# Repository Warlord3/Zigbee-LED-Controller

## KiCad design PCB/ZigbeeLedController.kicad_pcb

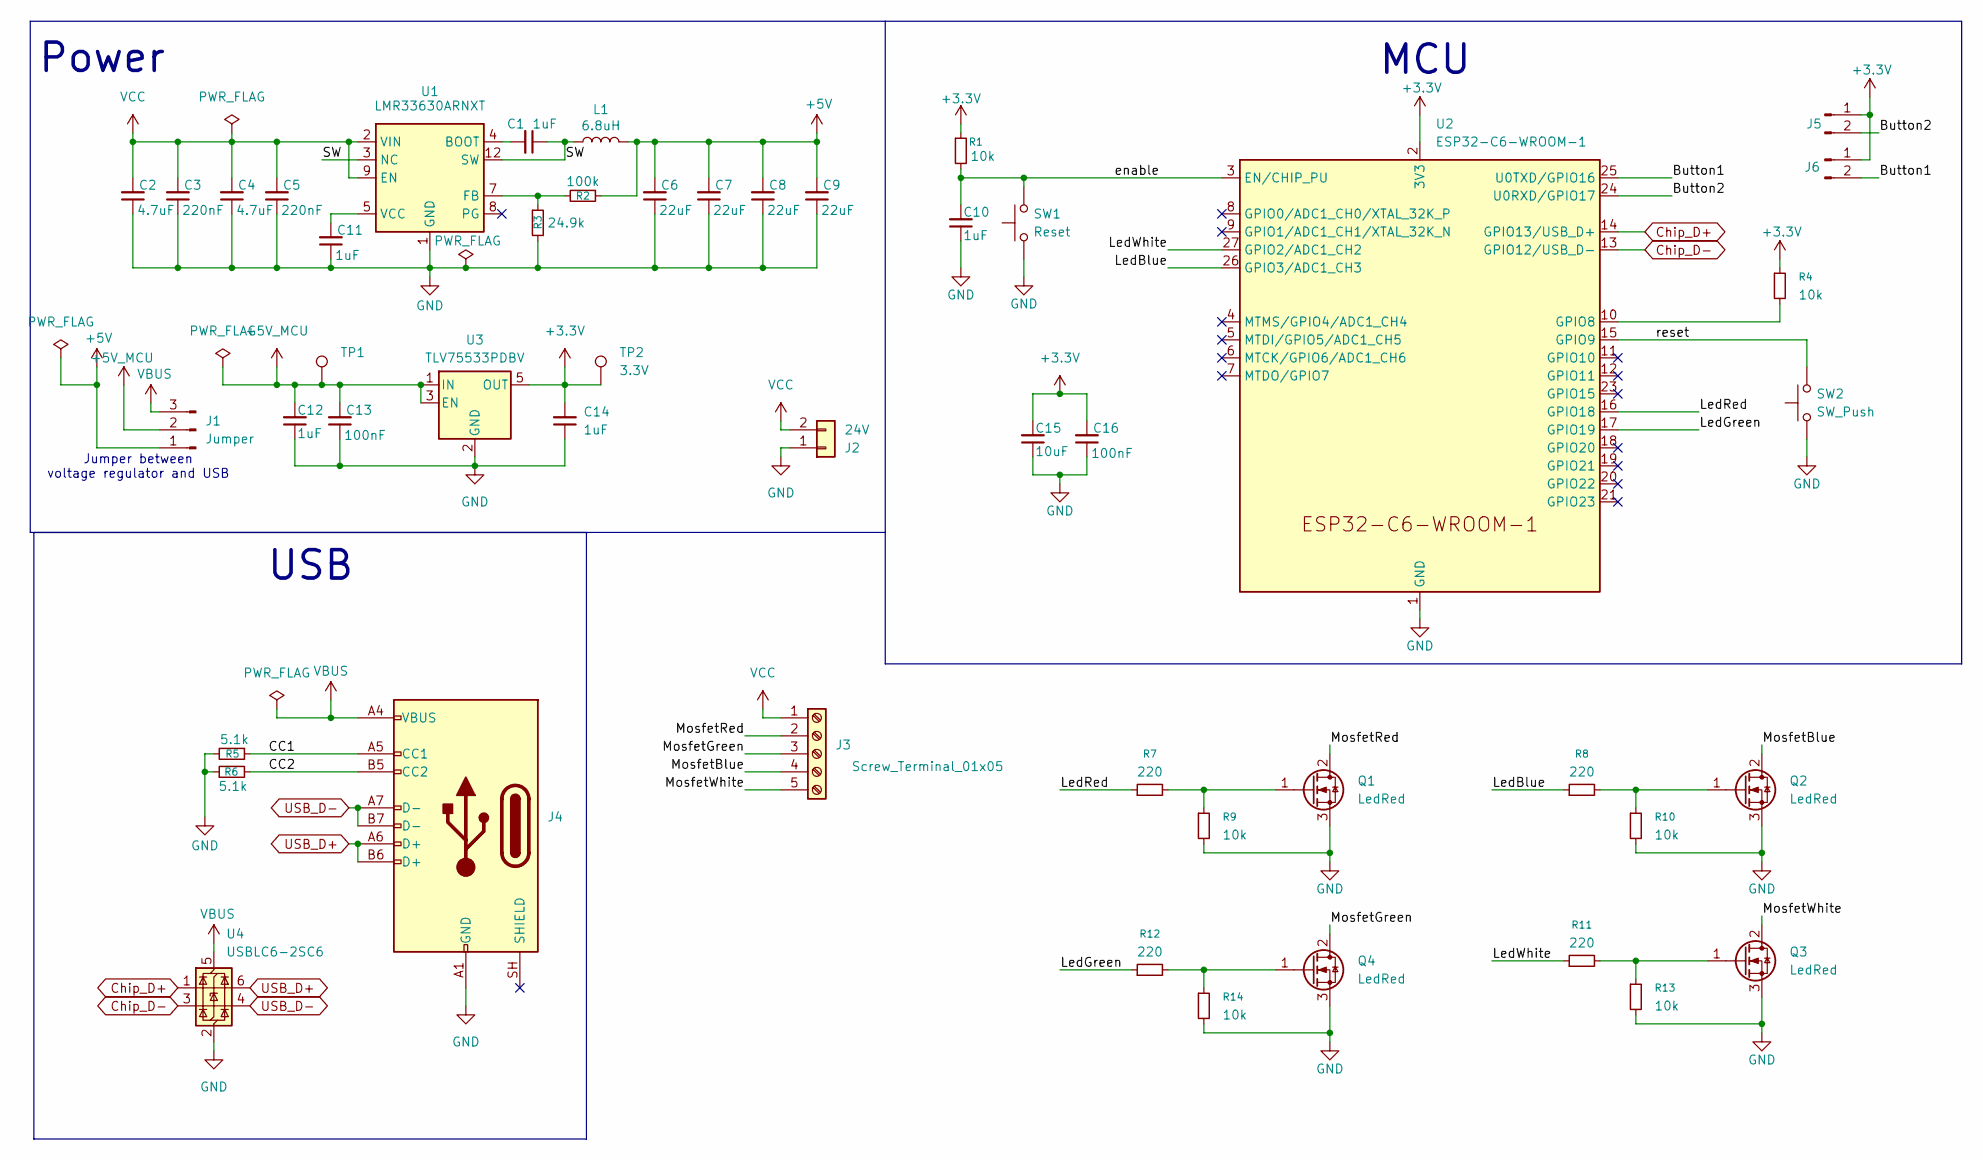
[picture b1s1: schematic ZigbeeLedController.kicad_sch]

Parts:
C1: 1uF; C_0603_1608Metric; MPN C29936
C2, C4: 4.7uF; C_0805_2012Metric; MPN C98192
C3, C5: 220nF; C_0603_1608Metric; MPN C307462
C6, C7, C8, C9: 22uF; C_1210_3225Metric; MPN C380537
C10, C12, C14: 1uF; C_0603_1608Metric; MPN C95843
C11: 1uF; C_0603_1608Metric; MPN C5199872
C13, C16: 100nF; C_0402_1005Metric; MPN C541406
C15: 10uF; C_0603_1608Metric; MPN C19702
J1: Jumper; PinHeader_1x03_P2.54mm_Vertical
J2: 24V; TerminalBlock_MaiXu_MX126-5.0-02P_1x02_P5.00mm; MPN C55469890
J3: Screw_Terminal_01x05; TerminalBlock_CUI_TB007-508-05_1x05_P5.08mm_Horizontal; MPN C2927513
J4: USB_C_Receptacle_USB2.0_14P; USB_C_Receptacle_G-Switch_GT-USB-7010ASV; MPN C2988369
J5, J6: Conn_01x02_Pin; PinHeader_1x02_P2.54mm_Vertical
L1: 6.8uH; L_TechFuse_SL0650; MPN C439010
Q1, Q2, Q3, Q4: LedRed; TO-252-2; MPN C49208668
R1, R4, R9, R10, R13, R14: 10k; R_0402_1005Metric; MPN C2906861
R2: 100k; R_0402_1005Metric; MPN C60491
R3: 24.9k; R_0402_1005Metric; MPN C2998048
R5, R6: 5.1k; R_0402_1005Metric; MPN C2906874
R7, R8, R11, R12: 220; R_0402_1005Metric; MPN C2909336
SW1: Reset; SW_SPST_TS-1088-xR020; MPN C455280
SW2: SW_Push; SW_SPST_TS-1088-xR020; MPN C455280
TP1: 5V; TestPoint_Pad_D1.5mm
TP2: 3.3V; TestPoint_Pad_D1.5mm
U1: LMR33630ARNXT; RNX0012B; MPN C1850374
U2: ESP32-C6-WROOM-1; MPN C6034714
U3: TLV75533PDBV; SOT-23-5; MPN C404027
U4: USBLC6-2SC6; SOT-23-6; MPN C21713975

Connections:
+3.3V: C14.2, C15.2, C16.2, J5.1, J6.1, R1.1, R4.1, TP2.1 (1_1), U2.2 (3V3), U3.5 (OUT)
+5V: C6.2, C7.2, C8.2, C9.2, J1.1, L1.2, R2.1
+5V_MCU: C12.2, C13.2, J1.2, TP1.1 (1_1), U3.1 (IN), U3.3 (EN)
/Button1: J6.2, U2.25 (U0TXD/GPIO16)
/Button2: J5.2, U2.24 (U0RXD/GPIO17)
/CC1: J4.A5 (CC1), R5.1
/CC2: J4.B5 (CC2), R6.2
/LedBlue: R8.1, U2.26 (GPIO3/ADC1_CH3)
/LedGreen: R12.1, U2.17 (GPIO19)
/LedRed: R7.1, U2.16 (GPIO18)
/LedWhite: R11.1, U2.27 (GPIO2/ADC1_CH2)
/MosfetBlue: J3.4, Q2.2 (D)
/MosfetGreen: J3.3, Q4.2 (D)
/MosfetRed: J3.2, Q1.2 (D)
/MosfetWhite: J3.5, Q3.2 (D)
/SW: C1.1, L1.1, U1.3 (NC), U1.12 (SW)
/enable: C10.2, R1.2, SW1.2, U2.3 (EN/CHIP_PU)
/reset: SW2.2, U2.15 (GPIO9)
Chip_D+: U2.14 (GPIO13/USB_D+), U4.1 (I/O1)
Chip_D-: U2.13 (GPIO12/USB_D-), U4.3 (I/O2)
GND: C2.1, C3.1, C4.1, C5.1, C6.1, C7.1, C8.1, C9.1, C10.1, C11.1, C12.1, C13.1, C14.1, C15.1, C16.1, J2.1, J4.A1 (GND), J4.A12 (GND), J4.B1 (GND), J4.B12 (GND), Q1.3 (S), Q2.3 (S), Q3.3 (S), Q4.3 (S), R3.2, R5.2, R6.1, R9.2, R10.2, R13.2, R14.2, SW1.1, SW2.1, U1.1 (GND), U1.6 (GND), U1.11 (GND), U2.1 (GND), U2.28 (GND), U2.29 (GND), U3.2 (GND), U4.2 (GND)
unnamed: Q1.1 (G), R7.2, R9.1
unnamed: Q2.1 (G), R8.2, R10.1
unnamed: Q3.1 (G), R11.2, R13.1
unnamed: Q4.1 (G), R12.2, R14.1
unnamed: C1.2, U1.4 (BOOT)
unnamed: R2.2, R3.1, U1.7 (FB)
unnamed: C11.2, U1.5 (VCC)
unnamed: R4.2, U2.10 (GPIO8)
USB_D+: J4.A6 (D+), J4.B6 (D+), U4.6 (I/O1)
USB_D-: J4.A7 (D-), J4.B7 (D-), U4.4 (I/O2)
VBUS: J1.3, J4.A4 (VBUS), J4.A9 (VBUS), J4.B4 (VBUS), J4.B9 (VBUS), U4.5 (VBUS)
VCC: C2.2, C3.2, C4.2, C5.2, J2.2, J3.1, U1.2 (VIN), U1.9 (EN), U1.10 (VIN)

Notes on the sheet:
Jumper between voltage regulator and USB
Power
USB
MCU

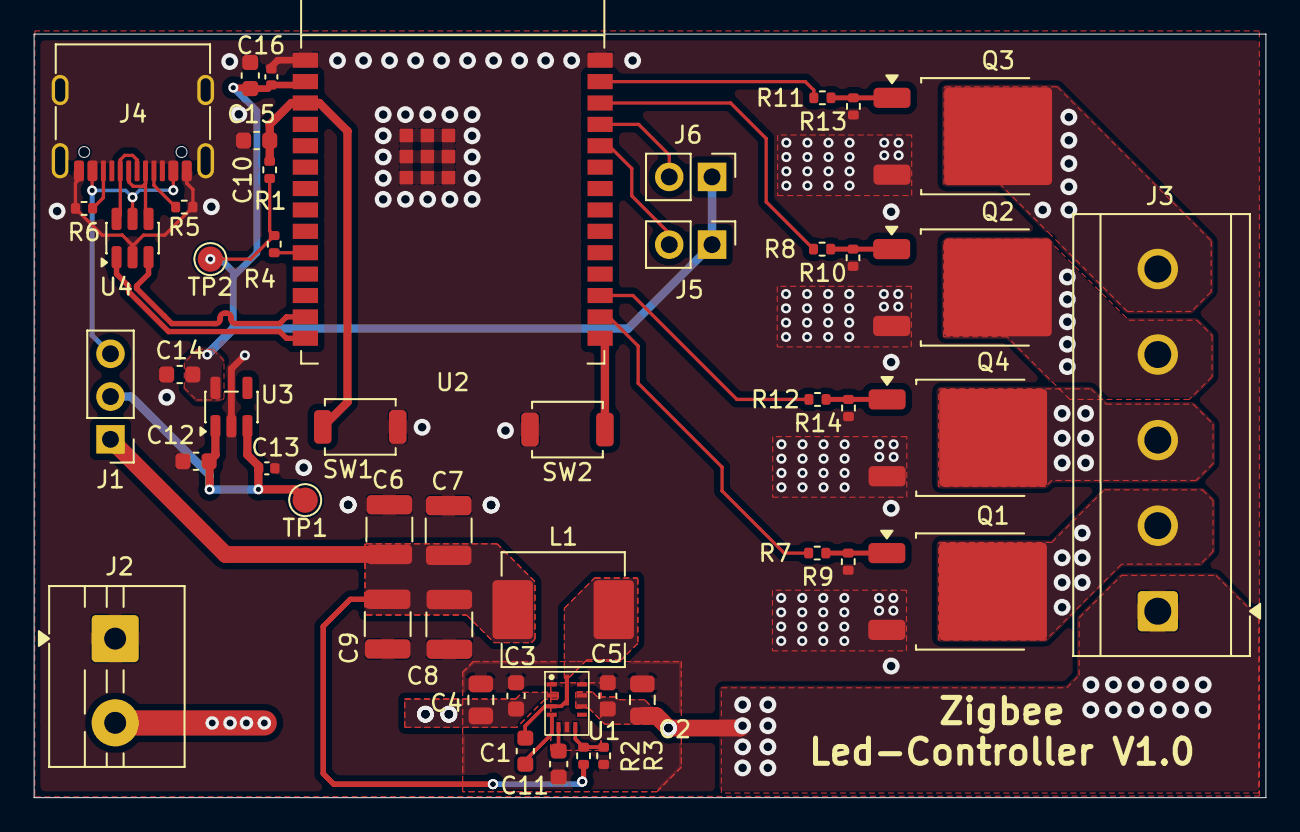
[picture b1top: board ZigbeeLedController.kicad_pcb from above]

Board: 4 copper layers, 73.1 x 45.3 mm, 49 parts (0 on the bottom side), 33 nets.
